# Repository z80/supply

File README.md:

supply
======

power supply board

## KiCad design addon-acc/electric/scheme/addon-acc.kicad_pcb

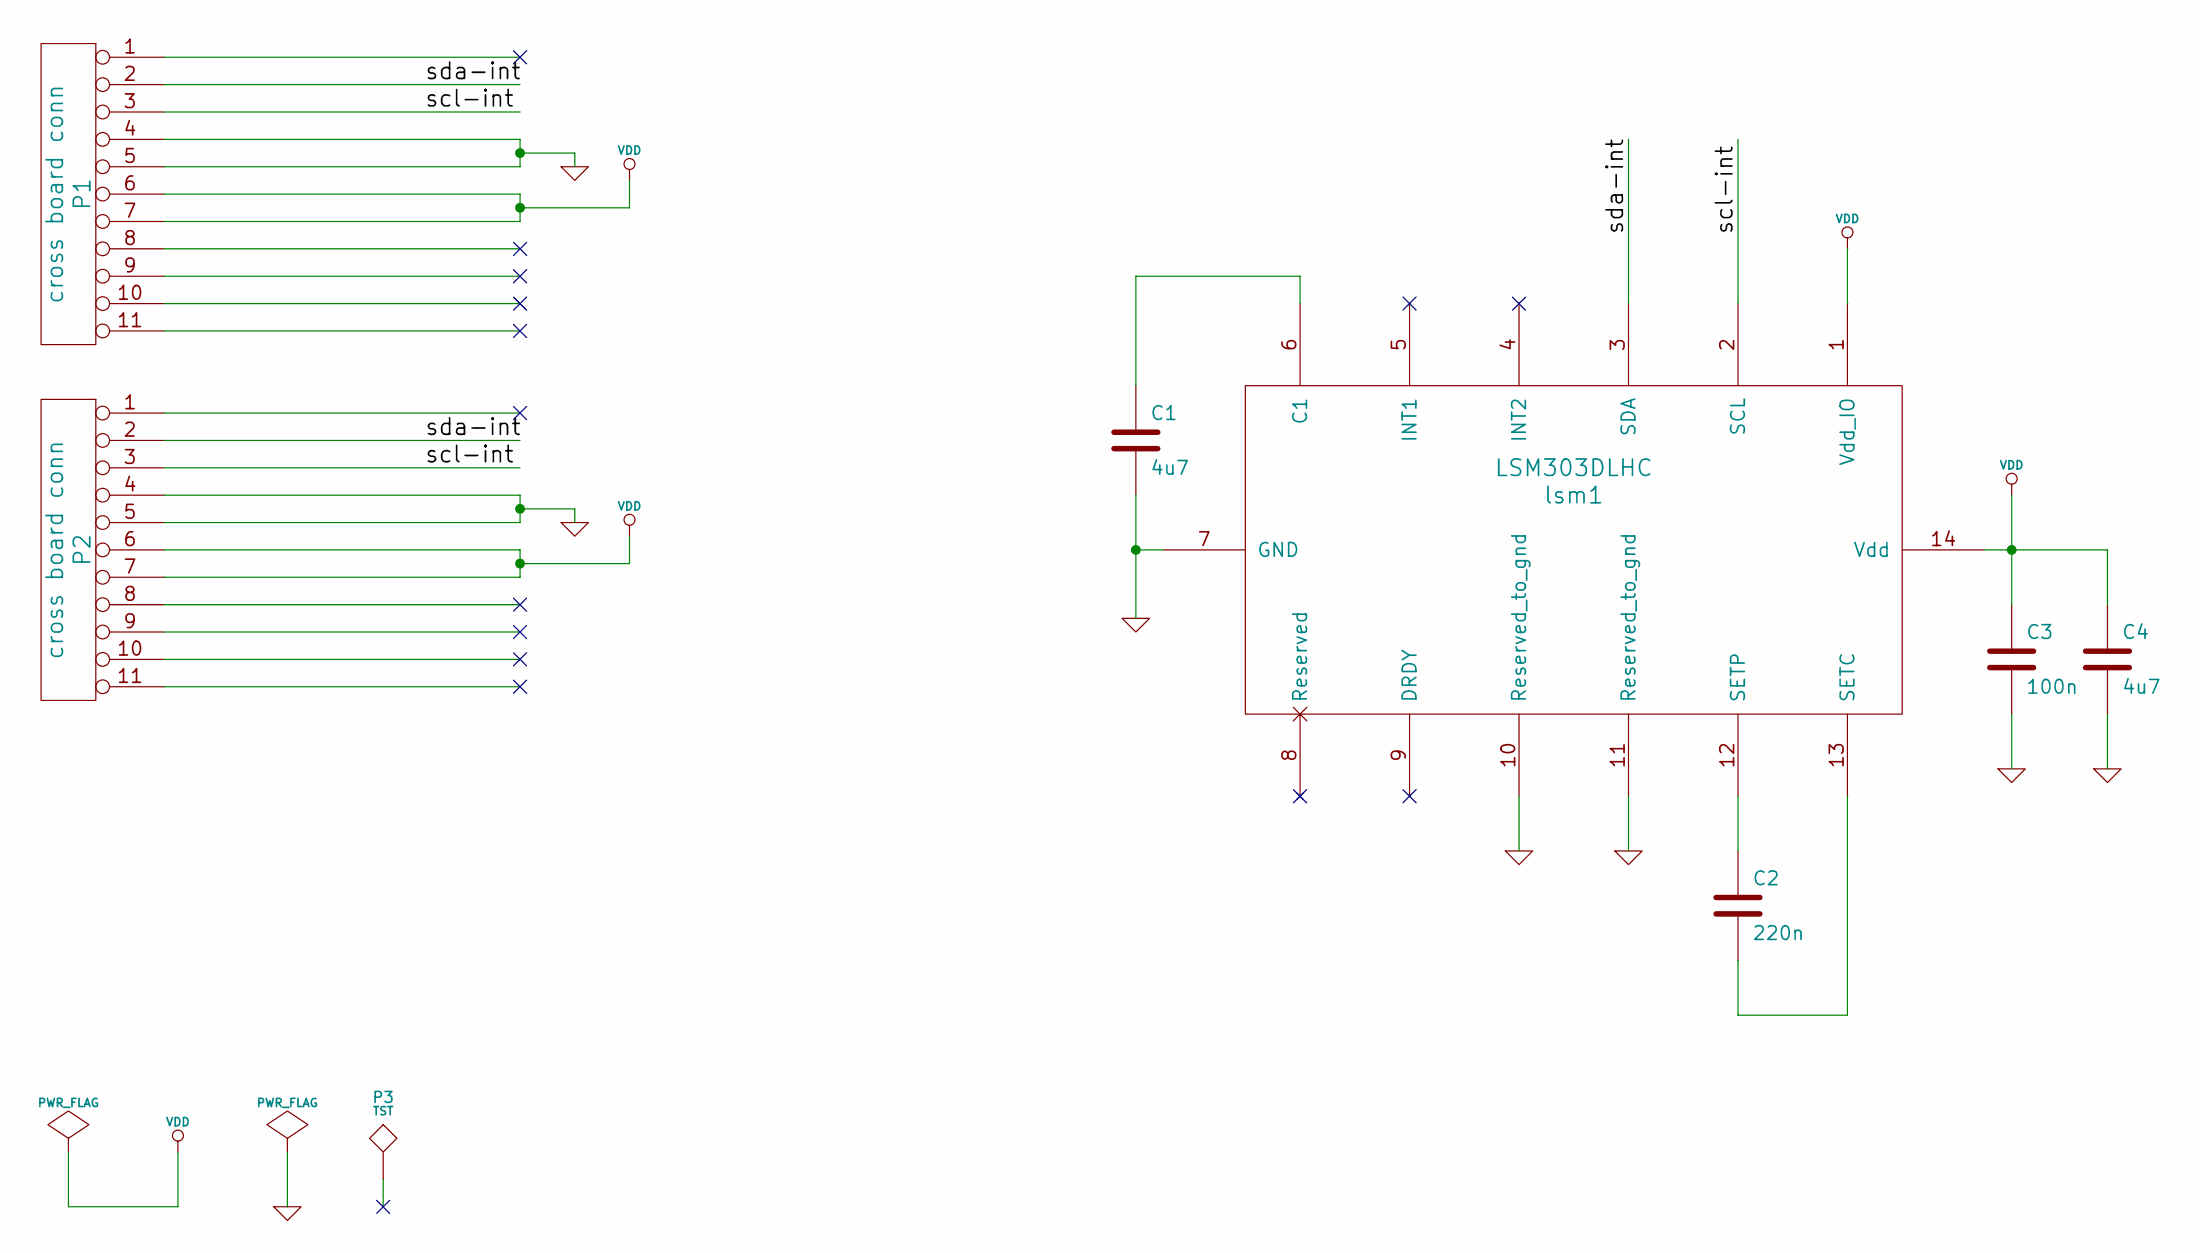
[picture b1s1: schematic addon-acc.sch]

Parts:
C1, C4: 4u7
C2: 220n
C3: 100n
P1, P2: cross board conn
P3: TST
lsm1: LSM303DLHC

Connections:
/scl-int: P1.3, P2.3, lsm1.2 (SCL)
/sda-int: P1.2, P2.2, lsm1.3 (SDA)
GND: C1.2, C3.2, C4.2, P1.4, P1.5, P2.4, P2.5, lsm1.7 (GND), lsm1.10 (Reserved_to_gnd), lsm1.11 (Reserved_to_gnd)
unnamed: C2.1, lsm1.12 (SETP)
unnamed: C1.1, lsm1.6 (C1)
unnamed: C2.2, lsm1.13 (SETC)
VDD: C3.1, C4.1, P1.6, P1.7, P2.6, P2.7, lsm1.1 (Vdd_IO), lsm1.14 (Vdd)

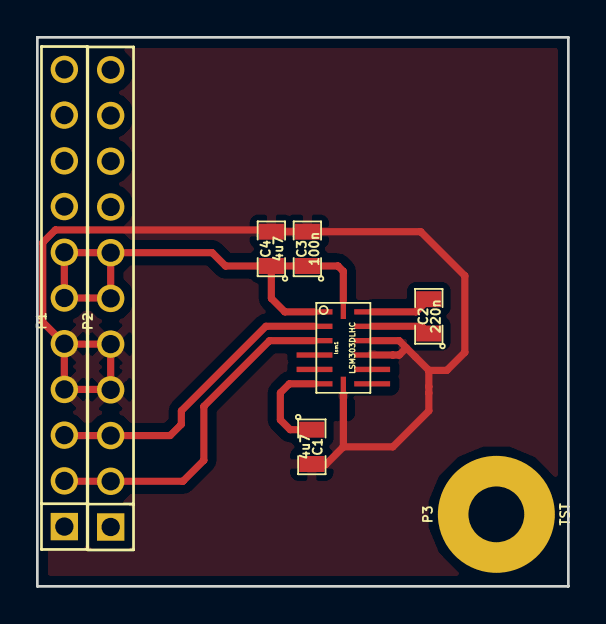
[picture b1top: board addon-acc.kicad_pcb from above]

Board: 2 copper layers, 29.5 x 30.5 mm, 8 parts (0 on the bottom side), 7 nets.

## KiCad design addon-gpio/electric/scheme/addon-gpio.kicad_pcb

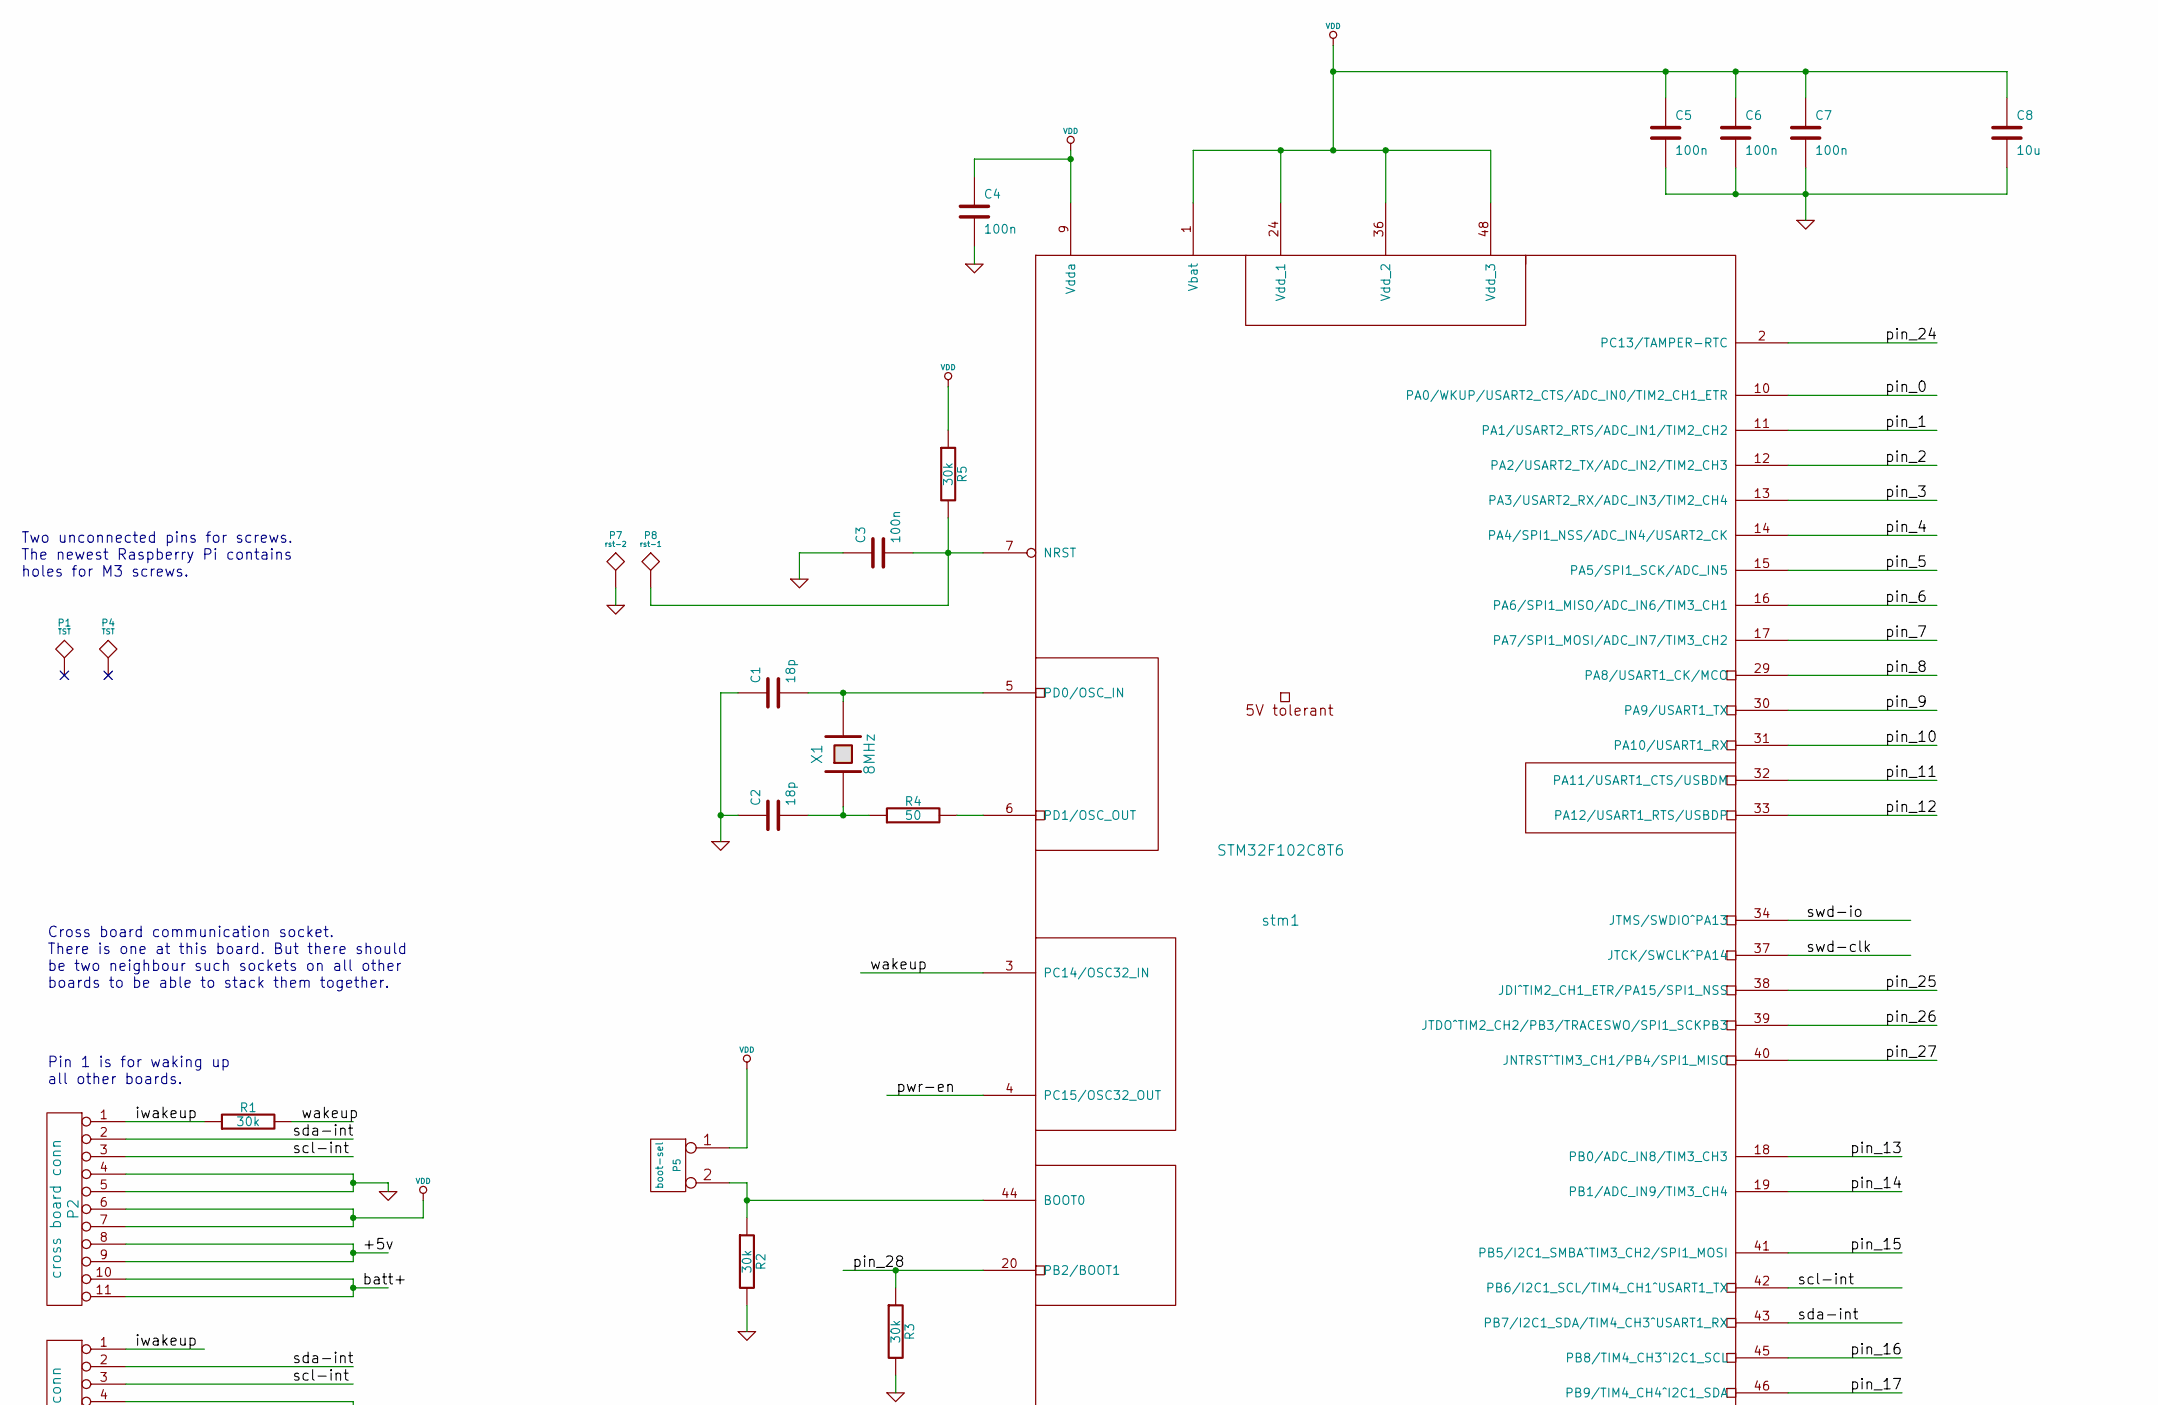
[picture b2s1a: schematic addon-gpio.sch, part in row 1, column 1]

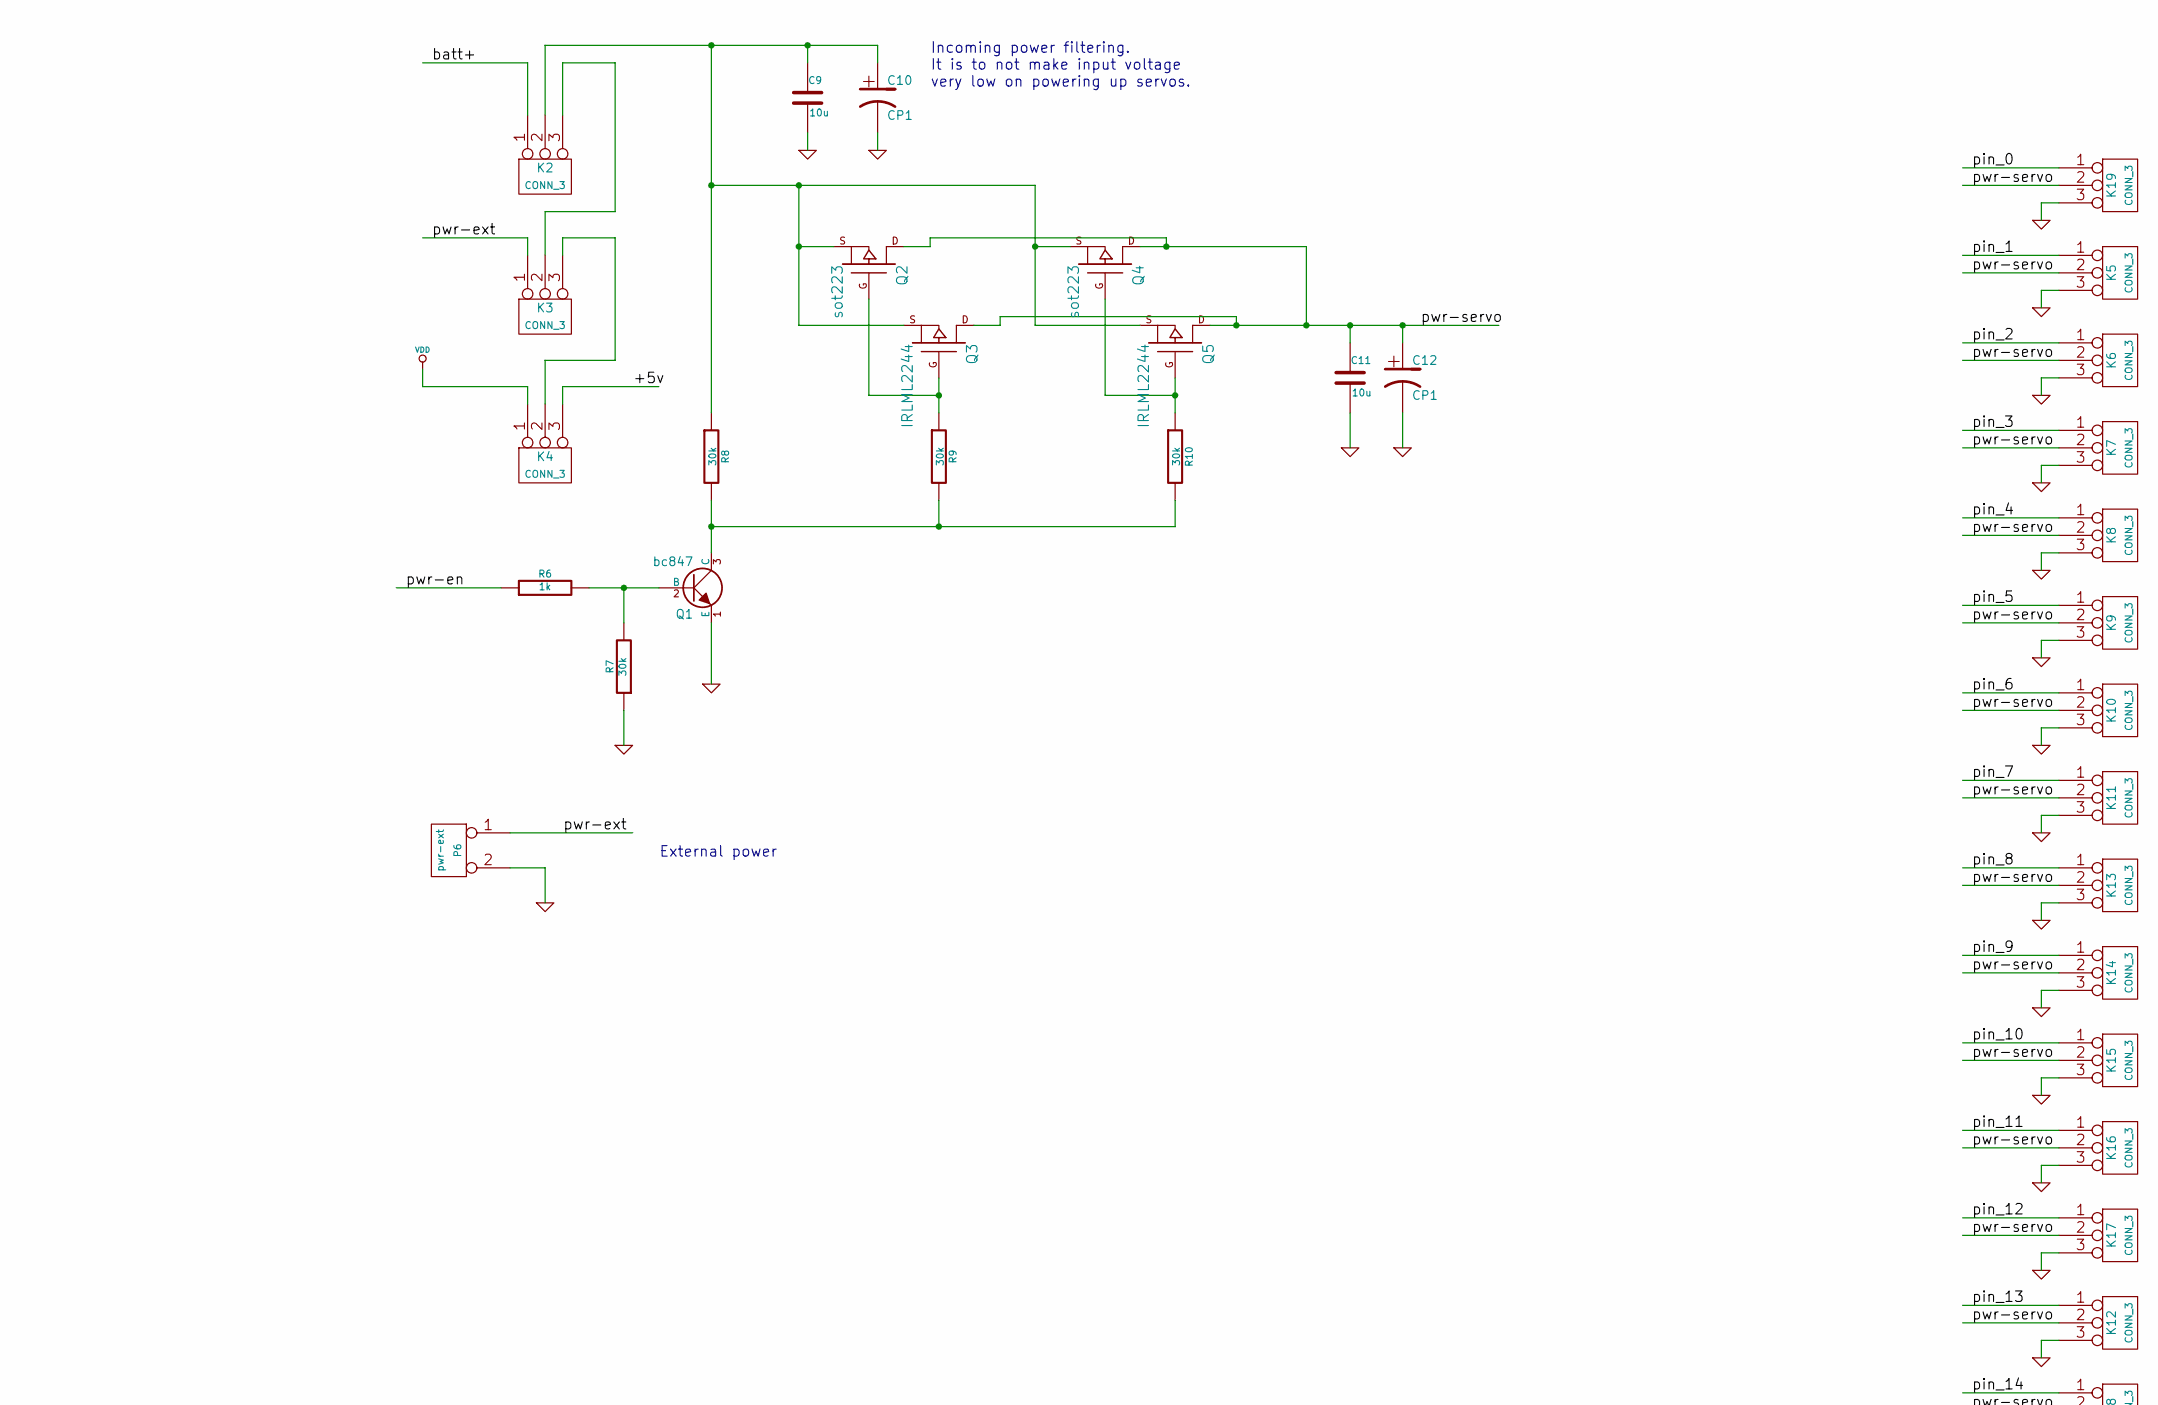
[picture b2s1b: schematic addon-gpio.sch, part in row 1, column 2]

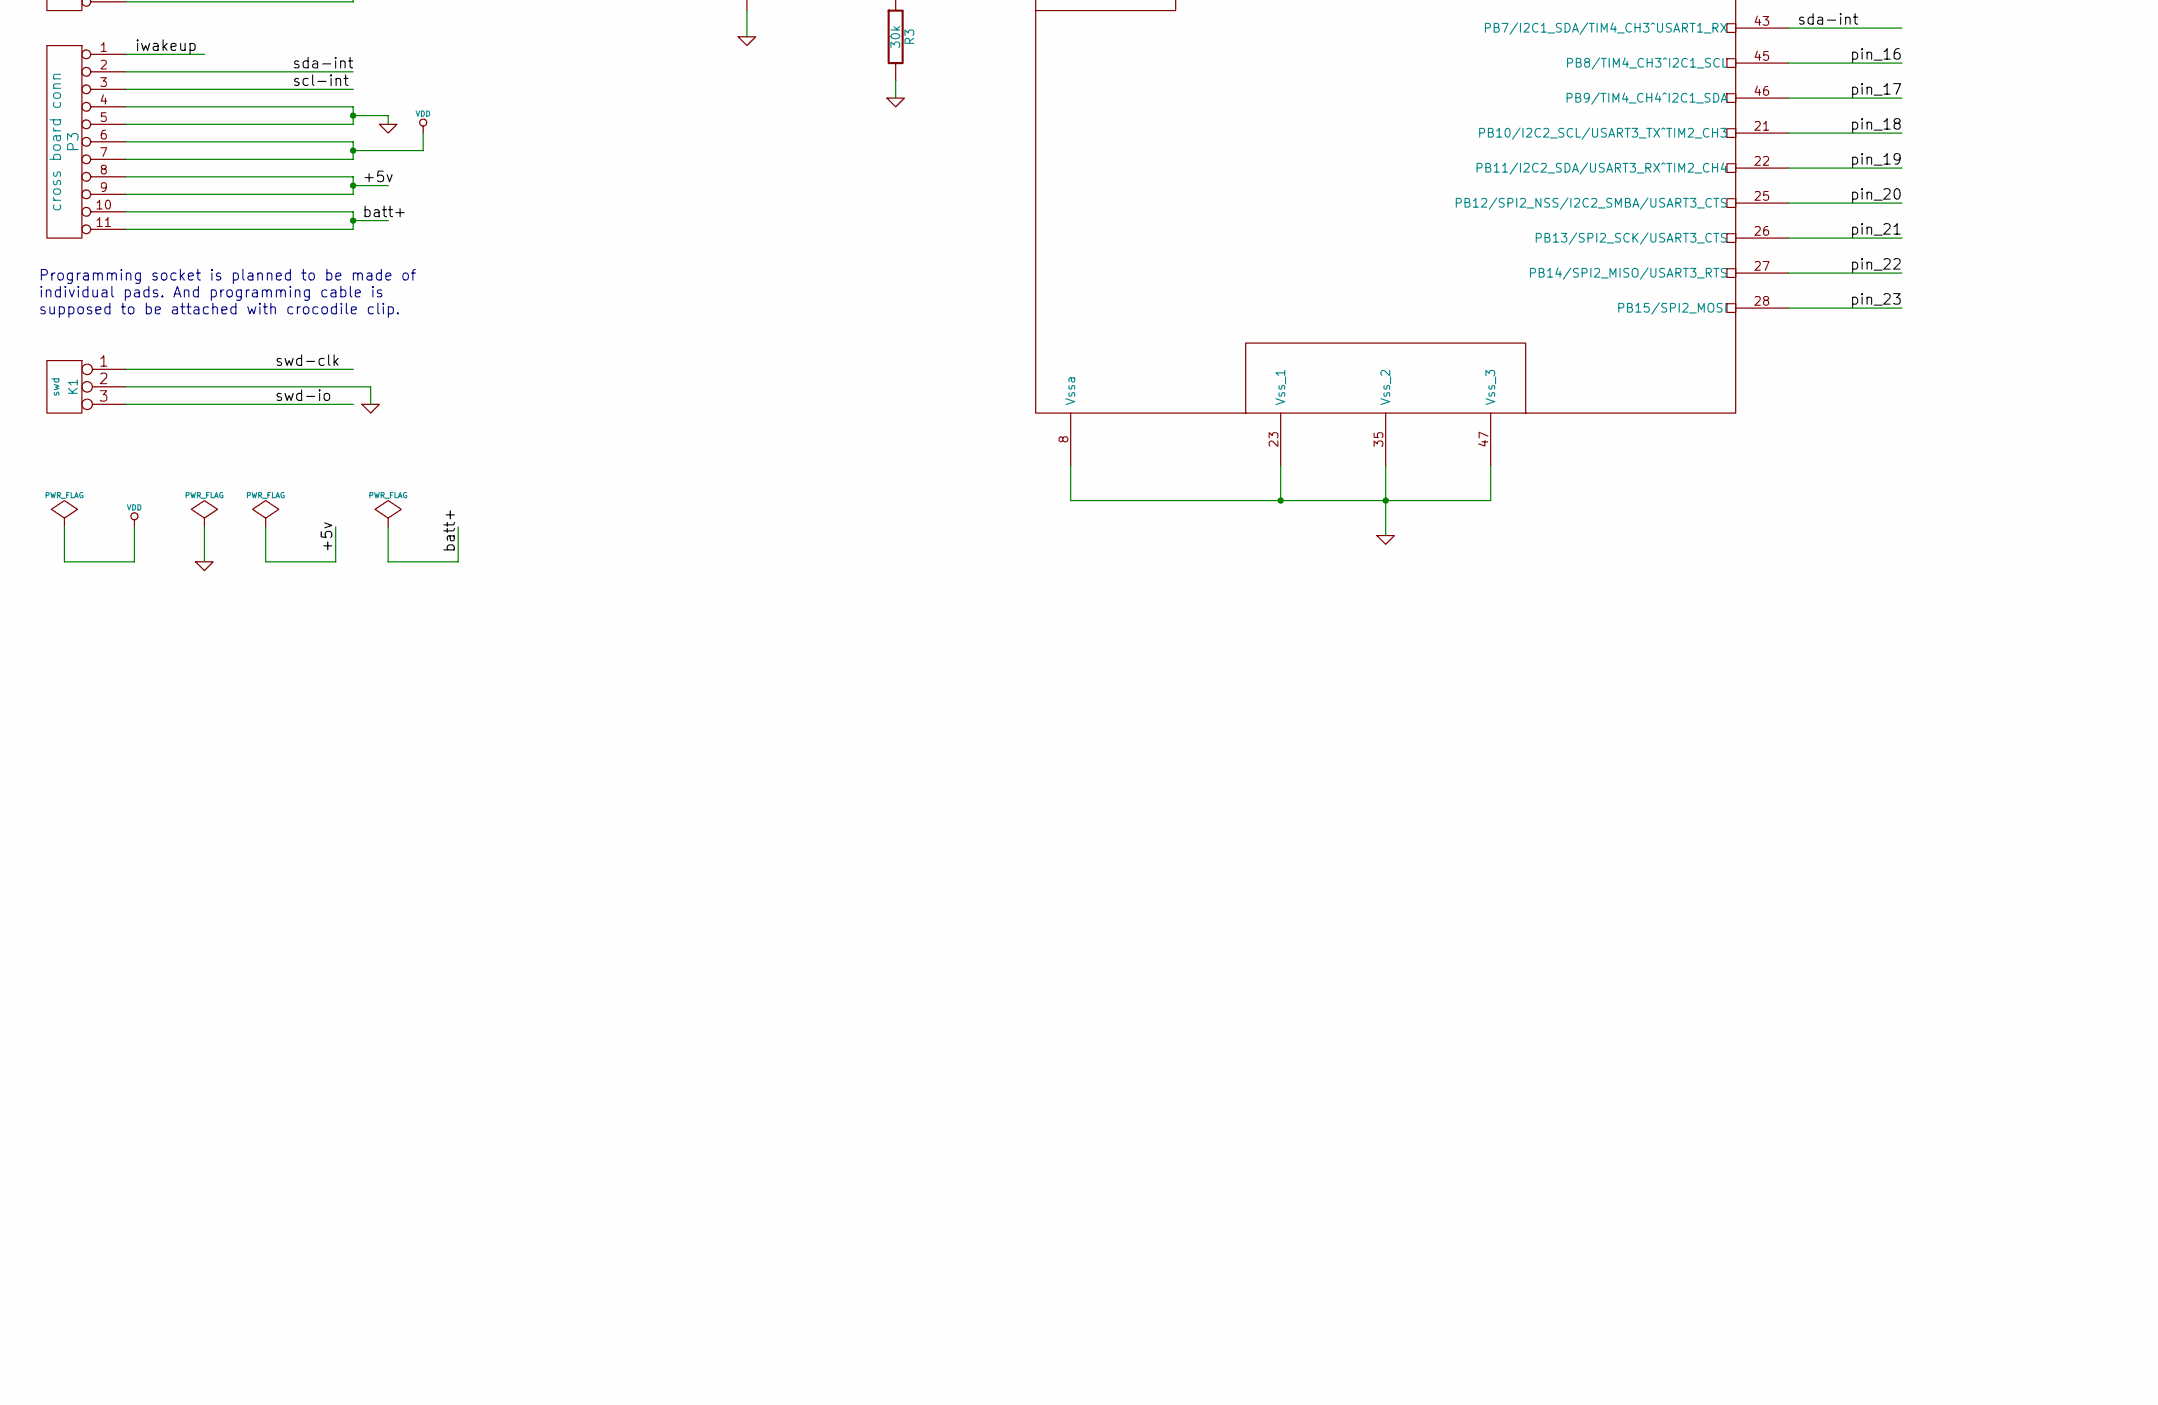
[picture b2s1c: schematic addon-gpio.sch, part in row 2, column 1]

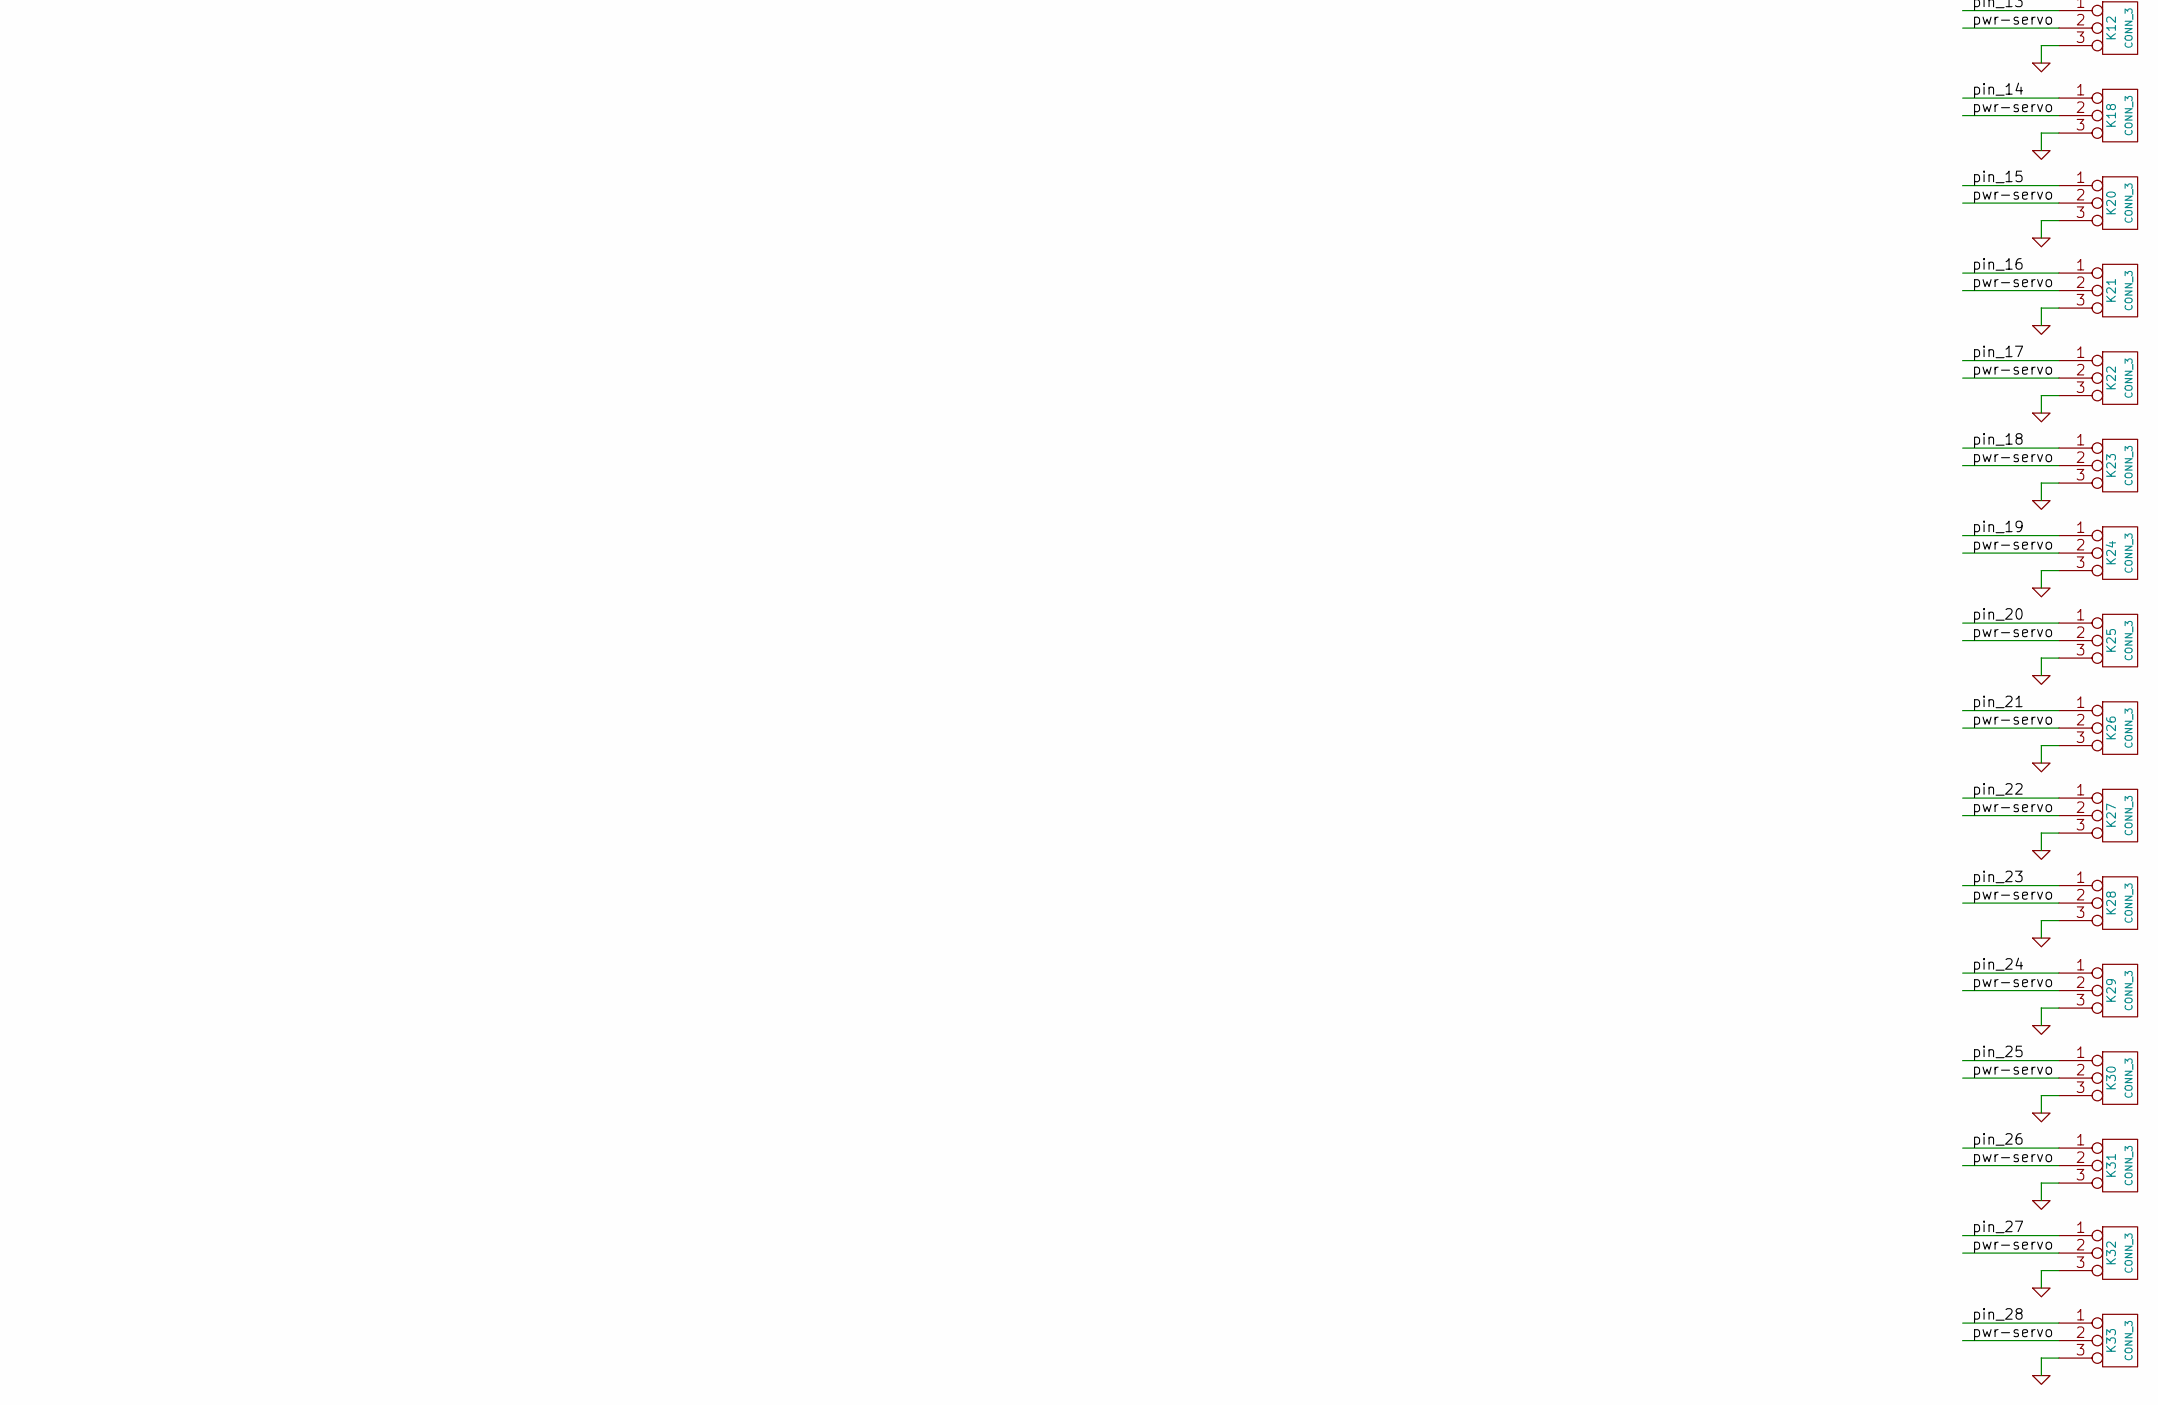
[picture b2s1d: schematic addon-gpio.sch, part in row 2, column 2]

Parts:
C1, C2: 18p
C3, C4, C5, C6, C7: 100n
C8: 10u
C9, C11: 10u
C10, C12: CP1
K1: swd
K2, K3, K4, K5, K6, K7, K8, K9, K10, K11, K12, K13, K14, K15, K16, K17, K18, K19, K20, K21, K22, K23, K24, K25, K26, K27, K28, K29, K30, K31, K32, K33: CONN_3
P1, P4: TST
P2, P3: cross board conn
P5: boot-sel
P6: pwr-ext
P7: rst-2
P8: rst-1
Q1: bc847
Q2, Q4: sot223
Q3, Q5: IRLML2244
R1, R2, R3, R5: 30k
R4: 50
R6: 1k
R7, R8, R9, R10: 30k
X1: 8MHz
stm1: STM32F102C8T6

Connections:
/+5v: K4.3, P2.8, P2.9, P3.8, P3.9
/batt+: K2.1, P2.10, P2.11, P3.10, P3.11
/iwakeup: P2.1, P3.1, R1.1
/pin_0: K19.1, stm1.10 (PA0/WKUP/USART2_CTS/ADC_IN0/TIM2_CH1_ETR)
/pin_1: K5.1, stm1.11 (PA1/USART2_RTS/ADC_IN1/TIM2_CH2)
/pin_2: K6.1, stm1.12 (PA2/USART2_TX/ADC_IN2/TIM2_CH3)
/pin_3: K7.1, stm1.13 (PA3/USART2_RX/ADC_IN3/TIM2_CH4)
/pin_4: K8.1, stm1.14 (PA4/SPI1_NSS/ADC_IN4/USART2_CK)
/pin_5: K9.1, stm1.15 (PA5/SPI1_SCK/ADC_IN5)
/pin_6: K10.1, stm1.16 (PA6/SPI1_MISO/ADC_IN6/TIM3_CH1)
/pin_7: K11.1, stm1.17 (PA7/SPI1_MOSI/ADC_IN7/TIM3_CH2)
/pin_8: K13.1, stm1.29 (PA8/USART1_CK/MCO)
/pin_9: K14.1, stm1.30 (PA9/USART1_TX)
/pin_10: K15.1, stm1.31 (PA10/USART1_RX)
/pin_11: K16.1, stm1.32 (PA11/USART1_CTS/USBDM)
/pin_12: K17.1, stm1.33 (PA12/USART1_RTS/USBDP)
/pin_13: K12.1, stm1.18 (PB0/ADC_IN8/TIM3_CH3)
/pin_14: K18.1, stm1.19 (PB1/ADC_IN9/TIM3_CH4)
/pin_15: K20.1, stm1.41 (PB5/I2C1_SMBA^TIM3_CH2/SPI1_MOSI)
/pin_16: K21.1, stm1.45 (PB8/TIM4_CH3^I2C1_SCL)
/pin_17: K22.1, stm1.46 (PB9/TIM4_CH4^I2C1_SDA)
/pin_18: K23.1, stm1.21 (PB10/I2C2_SCL/USART3_TX^TIM2_CH3)
/pin_19: K24.1, stm1.22 (PB11/I2C2_SDA/USART3_RX^TIM2_CH4)
/pin_20: K25.1, stm1.25 (PB12/SPI2_NSS/I2C2_SMBA/USART3_CTS)
/pin_21: K26.1, stm1.26 (PB13/SPI2_SCK/USART3_CTS)
/pin_22: K27.1, stm1.27 (PB14/SPI2_MISO/USART3_RTS)
/pin_23: K28.1, stm1.28 (PB15/SPI2_MOSI)
/pin_24: K29.1, stm1.2 (PC13/TAMPER-RTC)
/pin_25: K30.1, stm1.38 (JDI^TIM2_CH1_ETR/PA15/SPI1_NSS)
/pin_26: K31.1, stm1.39 (JTDO^TIM2_CH2/PB3/TRACESWO/SPI1_SCKPB3)
/pin_27: K32.1, stm1.40 (JNTRST^TIM3_CH1/PB4/SPI1_MISO)
/pin_28: K33.1, R3.1, stm1.20 (PB2/BOOT1)
/pwr-en: R6.1, stm1.4 (PC15/OSC32_OUT)
/pwr-ext: K3.1, P6.1
/pwr-servo: C11.1, C12.1, K5.2 (PM), K6.2 (PM), K7.2 (PM), K8.2 (PM), K9.2 (PM), K10.2 (PM), K11.2 (PM), K12.2 (PM), K13.2 (PM), K14.2 (PM), K15.2 (PM), K16.2 (PM), K17.2 (PM), K18.2 (PM), K19.2 (PM), K20.2 (PM), K21.2 (PM), K22.2 (PM), K23.2 (PM), K24.2 (PM), K25.2 (PM), K26.2 (PM), K27.2 (PM), K28.2 (PM), K29.2 (PM), K30.2 (PM), K31.2 (PM), K32.2 (PM), K33.2 (PM), Q2.D, Q3.D, Q4.D, Q5.D
/scl-int: P2.3, P3.3, stm1.42 (PB6/I2C1_SCL/TIM4_CH1^USART1_TX)
/sda-int: P2.2, P3.2, stm1.43 (PB7/I2C1_SDA/TIM4_CH3^USART1_RX)
/swd-clk: K1.1, stm1.37 (JTCK/SWCLK^PA14)
/swd-io: K1.3, stm1.34 (JTMS/SWDIO^PA13)
/wakeup: R1.2, stm1.3 (PC14/OSC32_IN)
GND: C1.1, C2.1, C3.1, C4.2, C5.2, C6.2, C7.2, C8.2, C9.2, C10.2, C11.2, C12.2, K1.2 (PM), K5.3, K6.3, K7.3, K8.3, K9.3, K10.3, K11.3, K12.3, K13.3, K14.3, K15.3, K16.3, K17.3, K18.3, K19.3, K20.3, K21.3, K22.3, K23.3, K24.3, K25.3, K26.3, K27.3, K28.3, K29.3, K30.3, K31.3, K32.3, K33.3, P2.4, P2.5, P3.4, P3.5, P6.2 (PM), P7.1, Q1.1 (E), R2.2, R3.2, R7.1, stm1.8 (Vssa), stm1.23 (Vss_1), stm1.35 (Vss_2), stm1.47 (Vss_3)
unnamed: K2.3, K3.2 (PM)
unnamed: K3.3, K4.2 (PM)
unnamed: C3.2, P8.1, R5.2, stm1.7 (NRST)
unnamed: P5.2 (PM), R2.1, stm1.44 (BOOT0)
unnamed: Q2.G, Q3.G, R9.1
unnamed: Q4.G, Q5.G, R10.1
unnamed: R4.2, stm1.6 (PD1/OSC_OUT)
unnamed: C2.2, R4.1, X1.1
unnamed: C1.2, X1.2, stm1.5 (PD0/OSC_IN)
unnamed: Q1.3 (C), R8.2, R9.2, R10.2
unnamed: C9.1, C10.1, K2.2 (PM), Q2.S, Q3.S, Q4.S, Q5.S, R8.1
unnamed: Q1.2 (B), R6.2, R7.2
VDD: C4.1, C5.1, C6.1, C7.1, C8.1, K4.1, P2.6, P2.7, P3.6, P3.7, P5.1, R5.1, stm1.1 (Vbat), stm1.9 (Vdda), stm1.24 (Vdd_1), stm1.36 (Vdd_2), stm1.48 (Vdd_3)

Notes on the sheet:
Programming socket is planned to be made of individual pads. And programming cable is supposed to be attached with crocodile clip.
Cross board communication socket. There is one at this board. But there should be two neighbour such sockets on all other boards to be able to stack them together.
Two unconnected pins for screws. The newest Raspberry Pi contains holes for M3 screws.
Pin 1 is for waking up all other boards.
External power
Incoming power filtering. It is to not make input voltage very low on powering up servos.

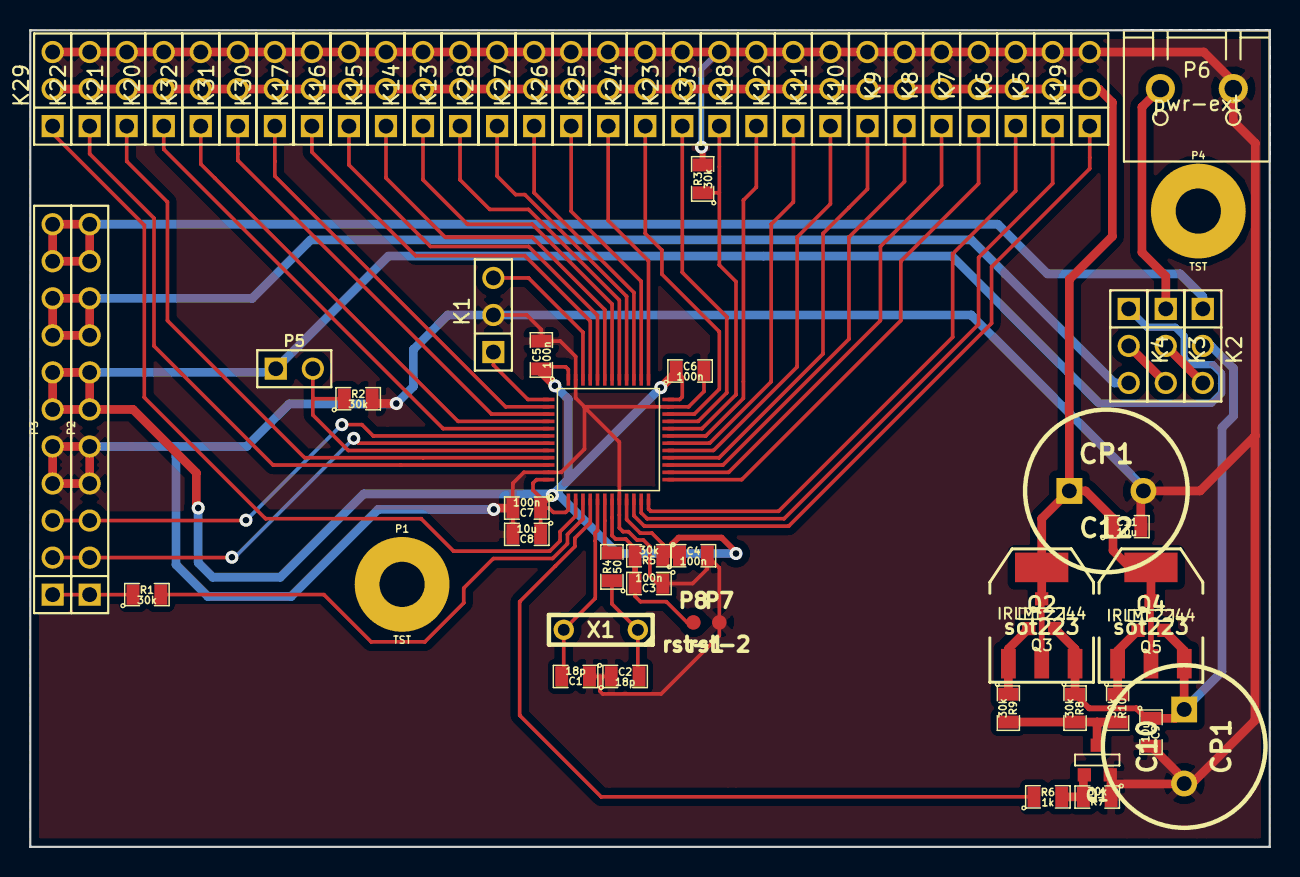
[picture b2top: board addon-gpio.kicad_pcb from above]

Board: 2 copper layers, 85.0 x 56.0 mm, 70 parts (0 on the bottom side), 54 nets.
